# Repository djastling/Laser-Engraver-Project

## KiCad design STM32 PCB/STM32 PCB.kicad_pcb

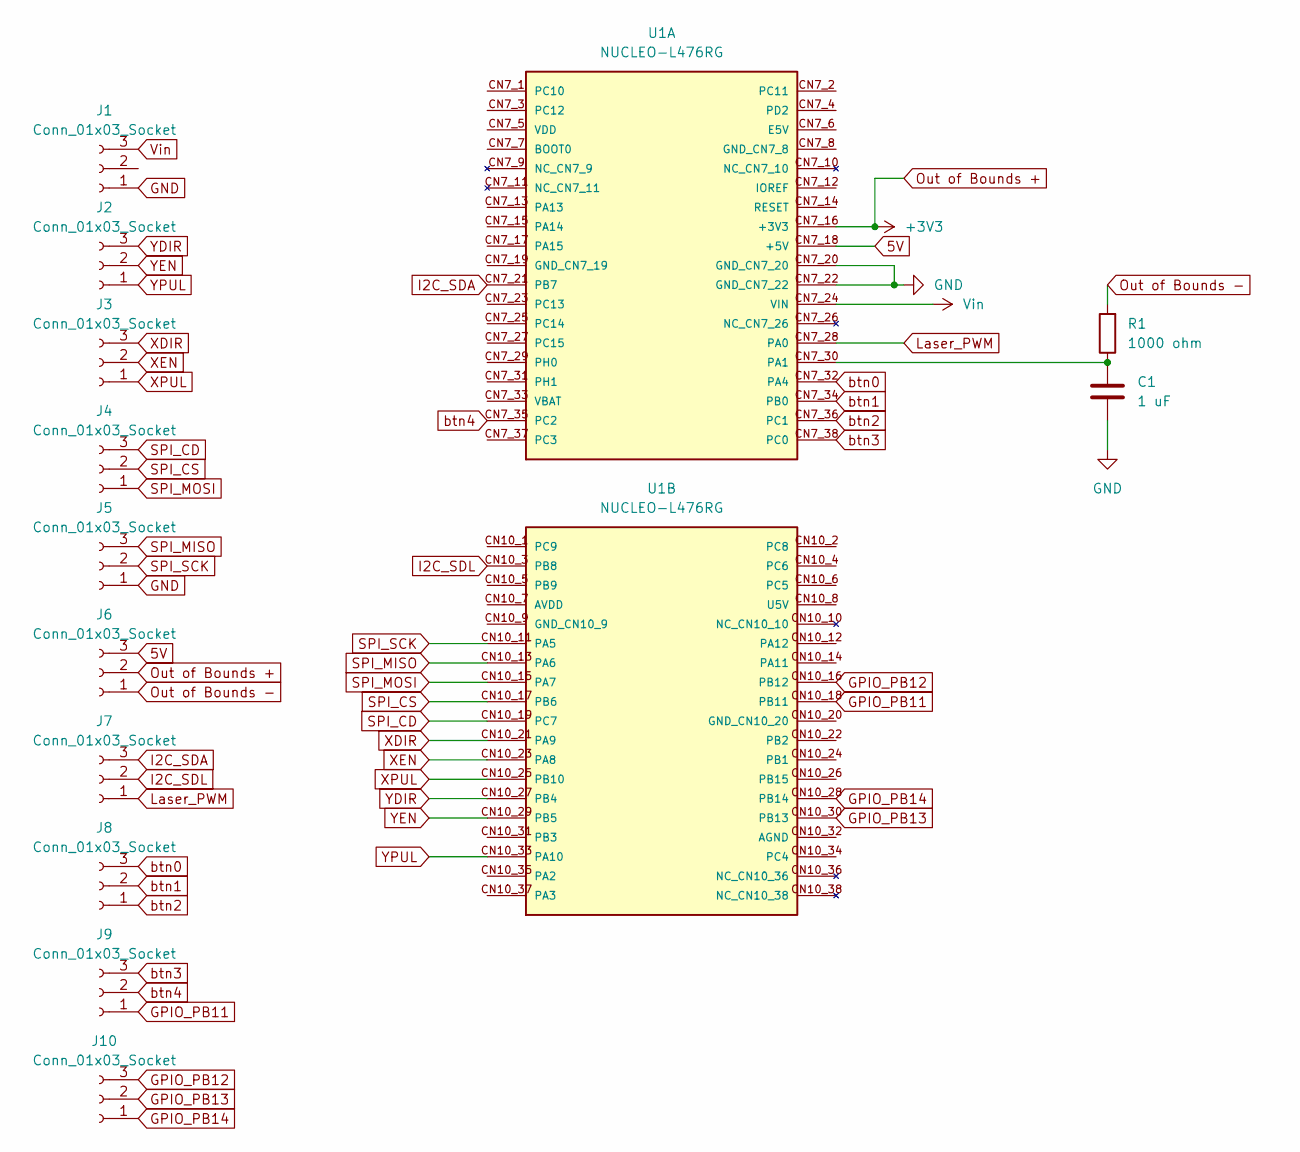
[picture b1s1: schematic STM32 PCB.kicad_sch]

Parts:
C1: 1 uF; C_0805_2012Metric_Pad1.18x1.45mm_HandSolder
J1, J2, J3, J4, J5, J6, J7, J8, J9, J10: Conn_01x03_Socket; PinHeader_1x03_P2.54mm_Vertical
R1: 1000 ohm; R_0805_2012Metric_Pad1.20x1.40mm_HandSolder
U1: NUCLEO-L476RG; MODULE_NUCLEO-L476RG; PARTREV 15

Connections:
5V: J6.3, U1.CN7_18 (+5V)
GND: C1.1, J1.1, J5.1, U1.CN7_20 (GND_CN7_20), U1.CN7_22 (GND_CN7_22)
GPIO_PB11: J9.1, U1.CN10_18 (PB11)
GPIO_PB12: J10.3, U1.CN10_16 (PB12)
GPIO_PB13: J10.2, U1.CN10_30 (PB13)
GPIO_PB14: J10.1, U1.CN10_28 (PB14)
I2C_SDA: J7.3, U1.CN7_21 (PB7)
I2C_SDL: J7.2, U1.CN10_3 (PB8)
Laser_PWM: J7.1, U1.CN7_28 (PA0)
unnamed: C1.2, R1.1, U1.CN7_30 (PA1)
Out of Bounds +: J6.2, U1.CN7_16 (+3V3)
Out of Bounds -: J6.1, R1.2
SPI_CD: J4.3, U1.CN10_19 (PC7)
SPI_CS: J4.2, U1.CN10_17 (PB6)
SPI_MISO: J5.3, U1.CN10_13 (PA6)
SPI_MOSI: J4.1, U1.CN10_15 (PA7)
SPI_SCK: J5.2, U1.CN10_11 (PA5)
Vin: J1.3, U1.CN7_24 (VIN)
XDIR: J3.3, U1.CN10_21 (PA9)
XEN: J3.2, U1.CN10_23 (PA8)
XPUL: J3.1, U1.CN10_25 (PB10)
YDIR: J2.3, U1.CN10_27 (PB4)
YEN: J2.2, U1.CN10_29 (PB5)
YPUL: J2.1, U1.CN10_33 (PA10)
btn0: J8.3, U1.CN7_32 (PA4)
btn1: J8.2, U1.CN7_34 (PB0)
btn2: J8.1, U1.CN7_36 (PC1)
btn3: J9.3, U1.CN7_38 (PC0)
btn4: J9.2, U1.CN7_35 (PC2)

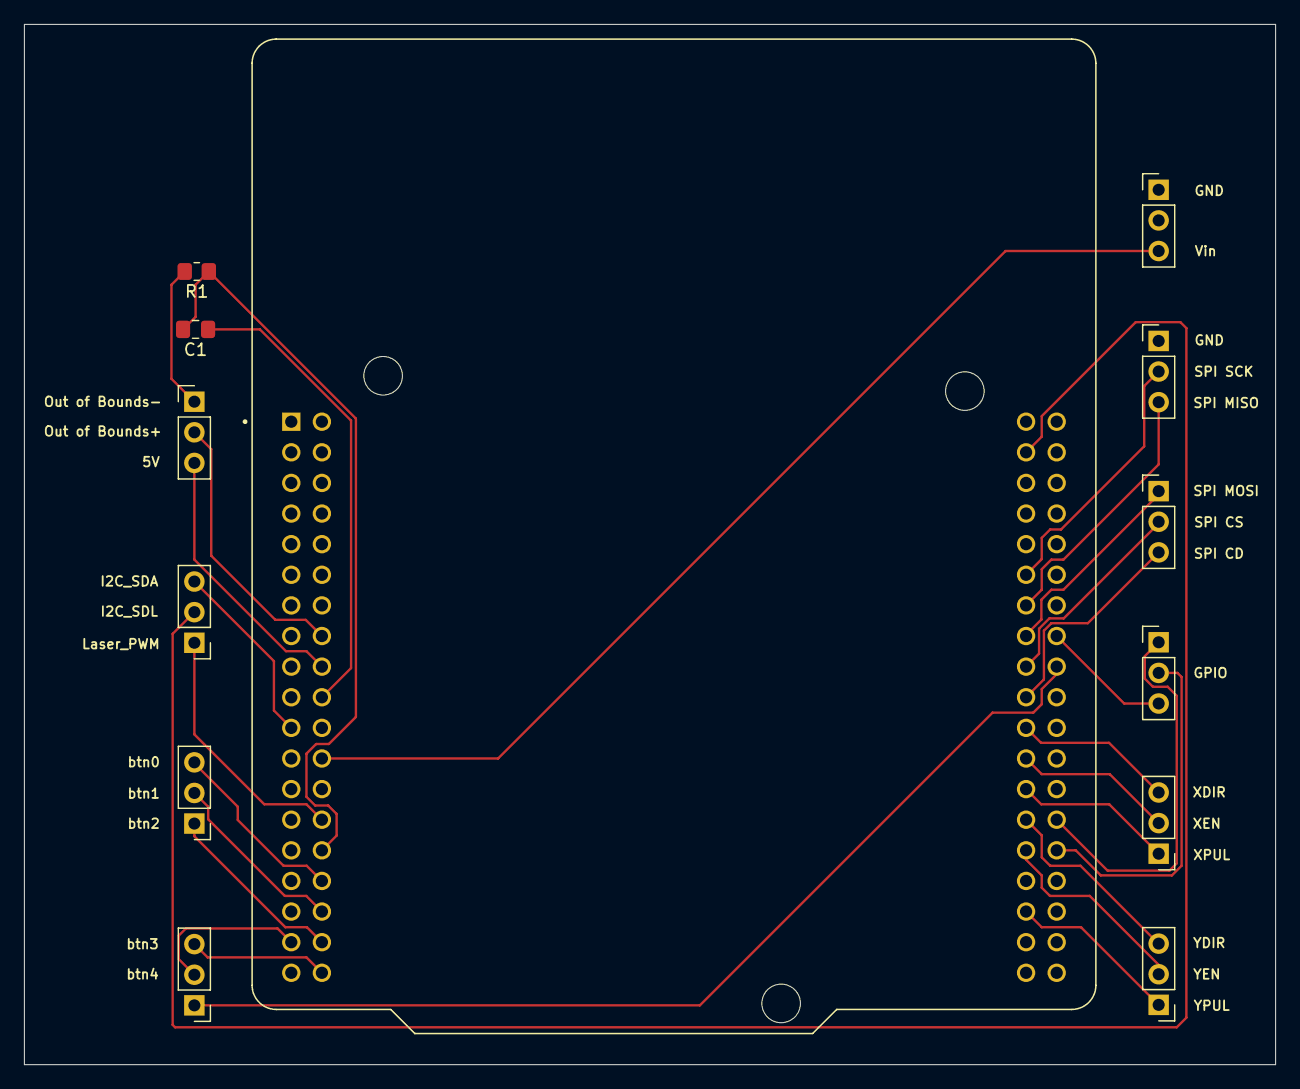
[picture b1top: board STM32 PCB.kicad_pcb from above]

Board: 2 copper layers, 103.8 x 86.3 mm, 13 parts (0 on the bottom side), 29 nets.

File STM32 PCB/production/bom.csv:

Designator,Footprint,Quantity,Value,LCSC Part #
C1,0805,1,1 uF,
"J1, J10, J2, J3, J4, J5, J6, J7, J8, J9",PinHeader_1x03_P2.54mm_Vertical,10,Conn_01x03_Socket,
R1,0805,1,1000 ohm,
U1,MODULE_NUCLEO-L476RG,1,NUCLEO-L476RG,

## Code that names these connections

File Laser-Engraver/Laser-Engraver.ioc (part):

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Mcu.Name=STM32L476R(C-E-G)Tx
Mcu.Package=LQFP64
Mcu.UserName=STM32L476RGTx
PA0.Signal=S_TIM2_CH1
PA1.GPIOParameters=GPIO_PuPd,GPIO_Label
PA1.GPIO_Label=shutdownButton
PA1.GPIO_PuPd=GPIO_PULLDOWN
PA1.Signal=GPXTI1
PA10.GPIOParameters=GPIO_Label
PA10.GPIO_Label=YPUL1
PA10.Signal=GPIO_Output
PA13\ (JTMS-SWDIO).GPIOParameters=GPIO_Label
PA13\ (JTMS-SWDIO).GPIO_Label=TMS
PA13\ (JTMS-SWDIO).Mode=Serial_Wire
PA13\ (JTMS-SWDIO).Signal=SYS_JTMS-SWDIO
PA14\ (JTCK-SWCLK).GPIOParameters=GPIO_Label
PA14\ (JTCK-SWCLK).GPIO_Label=TCK
PA14\ (JTCK-SWCLK).Mode=Serial_Wire
PA14\ (JTCK-SWCLK).Signal=SYS_JTCK-SWCLK
PA2.GPIOParameters=GPIO_Speed,GPIO_PuPd,GPIO_Label,GPIO_Mode
PA2.GPIO_Label=USART_TX
PA2.GPIO_Mode=GPIO_MODE_AF_PP
PA2.GPIO_PuPd=GPIO_NOPULL
PA2.GPIO_Speed=GPIO_SPEED_FREQ_VERY_HIGH
PA2.Mode=Asynchronous
PA2.Signal=USART2_TX
PA3.GPIOParameters=GPIO_Speed,GPIO_PuPd,GPIO_Label,GPIO_Mode
PA3.GPIO_Label=USART_RX
PA3.GPIO_Mode=GPIO_MODE_AF_PP
PA3.GPIO_PuPd=GPIO_NOPULL
PA3.GPIO_Speed=GPIO_SPEED_FREQ_VERY_HIGH
PA3.Mode=Asynchronous
PA3.Signal=USART2_RX
PA5.GPIOParameters=GPIO_Speed,GPIO_PuPd
PA5.GPIO_PuPd=GPIO_PULLUP
PA5.GPIO_Speed=GPIO_SPEED_FREQ_VERY_HIGH
PA5.Mode=Full_Duplex_Master
PA5.Signal=SPI1_SCK
PA6.GPIOParameters=GPIO_PuPd
PA6.GPIO_PuPd=GPIO_PULLUP
PA6.Mode=Full_Duplex_Master
PA6.Signal=SPI1_MISO
PA7.GPIOParameters=GPIO_PuPd
PA7.GPIO_PuPd=GPIO_PULLUP
PA7.Mode=Full_Duplex_Master
PA7.Signal=SPI1_MOSI
PA8.GPIOParameters=GPIO_Label
PA8.GPIO_Label=XEN
PA8.Signal=GPIO_Output
PA9.GPIOParameters=GPIO_Label
PA9.GPIO_Label=XDIR
PA9.Signal=GPIO_Output
PB10.GPIOParameters=GPIO_Label
PB10.GPIO_Label=XPUL
PB10.Signal=GPIO_Output
PB12.GPIOParameters=GPIO_Label
PB12.GPIO_Label=YPUL2
PB12.Signal=GPIO_Output
PB13.GPIOParameters=GPIO_Label
PB13.GPIO_Label=YEN2
PB13.Signal=GPIO_Output
PB14.GPIOParameters=GPIO_Label
PB14.GPIO_Label=YDIR2
PB14.Signal=GPIO_Output
PB3\ (JTDO-TRACESWO).GPIOParameters=GPIO_Label
PB3\ (JTDO-TRACESWO).GPIO_Label=SWO
PB3\ (JTDO-TRACESWO).Signal=SYS_JTDO-SWO
PB4\ (NJTRST).GPIOParameters=GPIO_Label
PB4\ (NJTRST).GPIO_Label=YDIR1
PB4\ (NJTRST).Signal=GPIO_Output
PB5.GPIOParameters=GPIO_Label
PB5.GPIO_Label=YEN1
PB5.Signal=GPIO_Output
PB6.GPIOParameters=PinState,GPIO_PuPd,GPIO_Label
PB6.GPIO_Label=SPI1_CS
PB6.GPIO_PuPd=GPIO_PULLUP
PB6.PinState=GPIO_PIN_SET
PB6.Signal=GPIO_Output
PB7.Mode=I2C
PB7.Signal=I2C1_SDA
PB8.Mode=I2C
PB8.Signal=I2C1_SCL
PC0.Signal=GPIO_Input
PC13.GPIOParameters=GPIO_PuPd,GPIO_Label,GPIO_ModeDefaultEXTI
PC13.GPIO_Label=B1 [Blue PushButton]
PC13.GPIO_ModeDefaultEXTI=GPIO_MODE_IT_FALLING
PC13.GPIO_PuPd=GPIO_NOPULL
PC13.Signal=GPXTI13
PC14-OSC32_IN\ (PC14).Mode=LSE-External-Oscillator
PC14-OSC32_IN\ (PC14).Signal=RCC_OSC32_IN
PC15-OSC32_OUT\ (PC15).Mode=LSE-External-Oscillator
PC15-OSC32_OUT\ (PC15).Signal=RCC_OSC32_OUT
PC7.GPIOParameters=GPIO_PuPd,GPIO_Label
PC7.GPIO_Label=SPI1_CD
PC7.GPIO_PuPd=GPIO_PULLUP
PC7.Signal=GPIO_Input
PH0-OSC_IN\ (PH0).Signal=RCC_OSC_IN
PH1-OSC_OUT\ (PH1).Signal=RCC_OSC_OUT
RCC.HSE_VALUE=8000000
RCC.SYSCLKFreq_VALUE=80000000
RCC.SYSCLKSource=RCC_SYSCLKSOURCE_PLLCLK
board=NUCLEO-L476RG
boardIOC=true

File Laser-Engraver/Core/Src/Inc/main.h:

/* USER CODE BEGIN Header */
/**
  ******************************************************************************
  * @file           : main.h
  * @brief          : Header for main.c file.
  *                   This file contains the common defines of the application.
  ******************************************************************************
  * @attention
  *
  * Copyright (c) 2025 STMicroelectronics.
  * All rights reserved.
  *
  * This software is licensed under terms that can be found in the LICENSE file
  * in the root directory of this software component.
  * If no LICENSE file comes with this software, it is provided AS-IS.
  *
  ******************************************************************************
  */
/* USER CODE END Header */

/* Define to prevent recursive inclusion -------------------------------------*/
#ifndef __MAIN_H
#define __MAIN_H

#ifdef __cplusplus
extern "C" {
#endif

/* Includes ------------------------------------------------------------------*/
#include "stm32l4xx_hal.h"

/* Private includes ----------------------------------------------------------*/
/* USER CODE BEGIN Includes */

/* USER CODE END Includes */

/* Exported types ------------------------------------------------------------*/
/* USER CODE BEGIN ET */

/* USER CODE END ET */

/* Exported constants --------------------------------------------------------*/
/* USER CODE BEGIN EC */

/* USER CODE END EC */

/* Exported macro ------------------------------------------------------------*/
/* USER CODE BEGIN EM */

/* USER CODE END EM */

void HAL_TIM_MspPostInit(TIM_HandleTypeDef *htim);

/* Exported functions prototypes ---------------------------------------------*/
void Error_Handler(void);

/* USER CODE BEGIN EFP */

/* USER CODE END EFP */

/* Private defines -----------------------------------------------------------*/
#define B1_Pin GPIO_PIN_13
#define B1_GPIO_Port GPIOC
#define B1_EXTI_IRQn EXTI15_10_IRQn
#define shutdownButton_Pin GPIO_PIN_0
#define shutdownButton_GPIO_Port GPIOA
#define shutdownButton_EXTI_IRQn EXTI0_IRQn
#define USART_TX_Pin GPIO_PIN_2
#define USART_TX_GPIO_Port GPIOA
#define USART_RX_Pin GPIO_PIN_3
#define USART_RX_GPIO_Port GPIOA
#define YPUL_Pin GPIO_PIN_10
#define YPUL_GPIO_Port GPIOB
#define SPI1_CD_Pin GPIO_PIN_7
#define SPI1_CD_GPIO_Port GPIOC
#define YEN_Pin GPIO_PIN_8
#define YEN_GPIO_Port GPIOA
#define YDIR_Pin GPIO_PIN_9
#define YDIR_GPIO_Port GPIOA
#define XPUL_Pin GPIO_PIN_10
#define XPUL_GPIO_Port GPIOA
#define TMS_Pin GPIO_PIN_13
#define TMS_GPIO_Port GPIOA
#define TCK_Pin GPIO_PIN_14
#define TCK_GPIO_Port GPIOA
#define SWO_Pin GPIO_PIN_3
#define SWO_GPIO_Port GPIOB
#define XDIR_Pin GPIO_PIN_4
#define XDIR_GPIO_Port GPIOB
#define XEN_Pin GPIO_PIN_5
#define XEN_GPIO_Port GPIOB
#define SPI1_CS_Pin GPIO_PIN_6
#define SPI1_CS_GPIO_Port GPIOB

/* USER CODE BEGIN Private defines */
#define SD_SPI_HANDLE hspi1

/* USER CODE END Private defines */

#ifdef __cplusplus
}
#endif

#endif /* __MAIN_H */

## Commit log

2025-02-14 Removed FreeRTOS and Added comments to code
    This code is currently working with a motor test loop
2025-02-18 added the shutdown switch
2025-03-04 Working SD card + G code parsing
2025-03-04 Update main.c
    Change
2025-03-05 Added initiate function
2025-03-10 Working code 3/10
2025-03-10 Adding The PWM code
2025-03-14 Working FreeRTOS code + comments
2025-03-17 I started the PCB on KiCad
2025-03-17 PCB upload
2025-03-18 KiCad PCB
2025-03-19 somewhat working initate function
2025-03-20 PCB updates
2025-03-21 kiCad final board upload
2025-03-24 reading names from files
2025-03-26 Working code to move x and y axis
2025-03-26 Fixed working code 3/25
2025-03-26 Working code with laser and both initiations working
2025-04-07 Changes up until our presentation
